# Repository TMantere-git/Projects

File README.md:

# Projects

Here is a compilation of projects I have been part of.

### 

Dartbot is a device that uses OpenGL to track a target and shoot a dart on it at a right distance. The target is taught to it using Haar Cascade. For moving it uses 4 DC motors, for target acquiring 2 servo motors, and for shooting the dart 2 dc motors and a solenoid. At a heart of the device lies a Raspberry Pi 3b and for camera it uses a regular Raspberry Pi camera.

Dartbot was part of a Amazing Robots competition hosted by Finnish TIETOTEKNIIKAN JA ELEKTRONIIKAN SEURA or SOCIETY OF INFORMATION TECHNOLOGY AND ELECTRONICS in which the robot came on the 4th position out of 10 competitors.

[Link to a News article about the competition](https://www.mikrobitti.fi/neuvot/robotit-kisasivat-messukeskuksessa-10-000-euron-voittopotti-tuli-ylivertaisella-teknisella-toteutuksella/60490a0f-0bc4-4c8e-a108-126306718576) (only in Finnish)

Picture of the Device

### 

Weatherstation is simple multidevice weather monitoring system. It uses multiple similar stations that are made of Adafruit Feather Huzzah ESP8266 boards with bme280 sensors to measure temperature, air pressure and air humidity. These measurements are then uploaded on a mySQL database every hour where they can be accessed by a website showing the data in raw form as well as in a graph.

Station-program runs on linux server that is self built, configurated and managed. On the server program does averaging of the measurements and a prediction of the weather using SARIMA model.

Website layout

### 

Basic snake type game using c#. To run the program run SnakeGame.exe from SnakeGame/bin/Release/publish/

Aim of the project was to learn some basic game-programming on C#

### 

TankkaajaPro is a self made android application to track car fueling statistics like kilometers driven, gas price, etc.
Application is done using dart and kotlin.
Application uses python api on a self made server to add and read data from mySQL database.

The aim of the project was to learn how to do android programming.

### 5 More to come...

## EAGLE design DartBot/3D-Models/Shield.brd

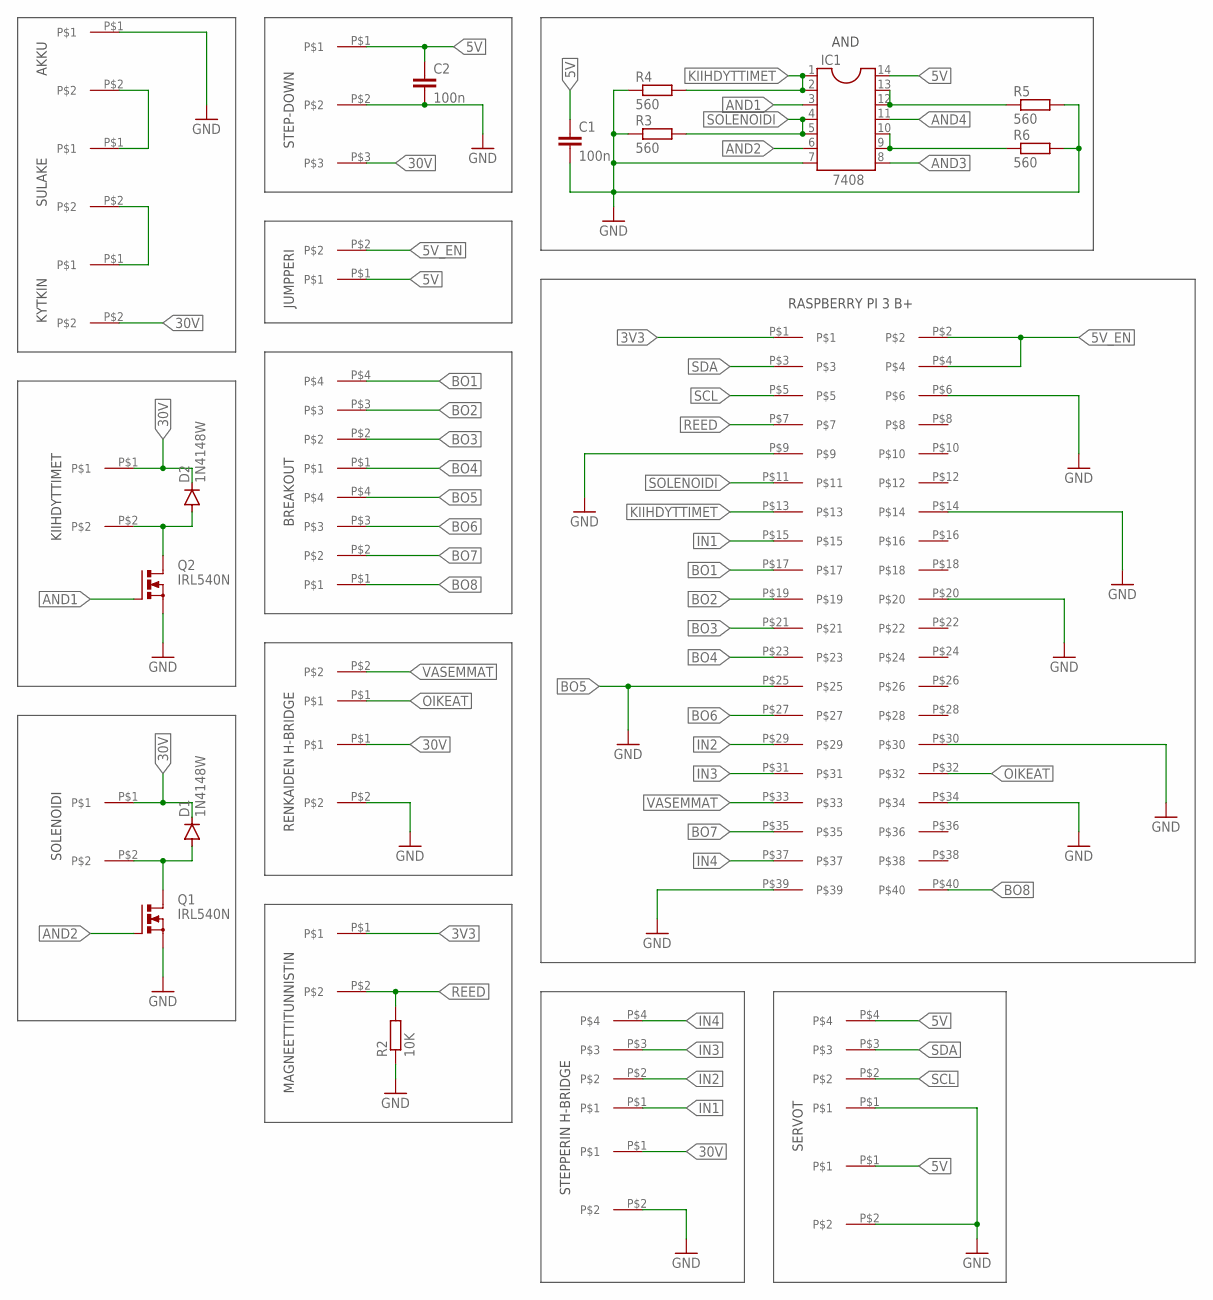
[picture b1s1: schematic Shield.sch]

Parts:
AKKU: AKKU; 2PIN
C1, C2: 100n; C1206
D1, D2: 1N4148W; SOD-123_MINI-SMA
IC1: 7408; DIL14
Q1, Q2: IRL540N; TO220BH
R2: 10K; M1206
R3, R4, R5, R6: 560; M1206
U$1: KIIHDYTTIMET; 2PIN
U$2: SOLENOIDI; 2PIN
U$3: 2.54_4PIN
U$4: SULAKE; 2PIN
U$5: KYTKIN; 2PIN
U$6: REED; 2PIN
U$7: STEP-DOWN; 3PIN
U$8: STEPPER; 2PIN
U$9: RENKAAT; 2PIN
U$10, U$11: 2.54_2PIN2PIN; 2.54_2PIN
U$12, U$15, U$16: SERVO; 2.54_4PIN
U$13: SERVO; 2PIN
U$14: PI3

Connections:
3V3: U$6.P$1, U$14.P$1
5V: C1.1, C2.1, IC1.14, U$7.P$1, U$11.P$1, U$12.P$4, U$13.P$1
5V_EN: U$11.P$2, U$14.P$2, U$14.P$4
30V: D1.C, D2.C, U$1.P$1, U$2.P$1, U$5.P$2, U$7.P$3, U$8.P$1, U$9.P$1
AND1: IC1.3, Q2.G
AND2: IC1.6, Q1.G
AND3: IC1.8
AND4: IC1.11
BO1: U$14.P$17, U$15.P$4
BO2: U$14.P$19, U$15.P$3
BO3: U$14.P$21, U$15.P$2
BO4: U$14.P$23, U$15.P$1
BO5: U$14.P$25, U$16.P$4
BO6: U$14.P$27, U$16.P$3
BO7: U$14.P$35, U$16.P$2
BO8: U$14.P$40, U$16.P$1
GND: AKKU.P$1, C1.2, C2.2, IC1.7, Q1.S, Q2.S, R2.1, R3.1, R4.1, R5.2, R6.2, U$7.P$2, U$8.P$2, U$9.P$2, U$12.P$1, U$13.P$2, U$14.P$6, U$14.P$9, U$14.P$14, U$14.P$20, U$14.P$30, U$14.P$34, U$14.P$39
IN1: U$3.P$1, U$14.P$15
IN2: U$3.P$2, U$14.P$29
IN3: U$3.P$3, U$14.P$31
IN4: U$3.P$4, U$14.P$37
KIIHDYTTIMET: IC1.1, IC1.2, R4.2, U$14.P$13
unnamed: D2.A, Q2.D, U$1.P$2
unnamed: IC1.9, IC1.10, R6.1
unnamed: IC1.12, IC1.13, R5.1
unnamed: D1.A, Q1.D, U$2.P$2
unnamed: AKKU.P$2, U$4.P$1
unnamed: U$4.P$2, U$5.P$1
OIKEAT: U$10.P$1, U$14.P$32
REED: R2.2, U$6.P$2, U$14.P$7
SCL: U$12.P$2, U$14.P$5
SDA: U$12.P$3, U$14.P$3
SOLENOIDI: IC1.4, IC1.5, R3.2, U$14.P$11
VASEMMAT: U$10.P$2, U$14.P$33

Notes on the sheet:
KIIHDYTTIMET
SOLENOIDI
AND
AKKU
SULAKE
KYTKIN
STEP-DOWN
STEPPERIN H-BRIDGE
RENKAIDEN H-BRIDGE
JUMPPERI
BREAKOUT
SERVOT
MAGNEETTITUNNISTIN
RASPBERRY PI 3 B+

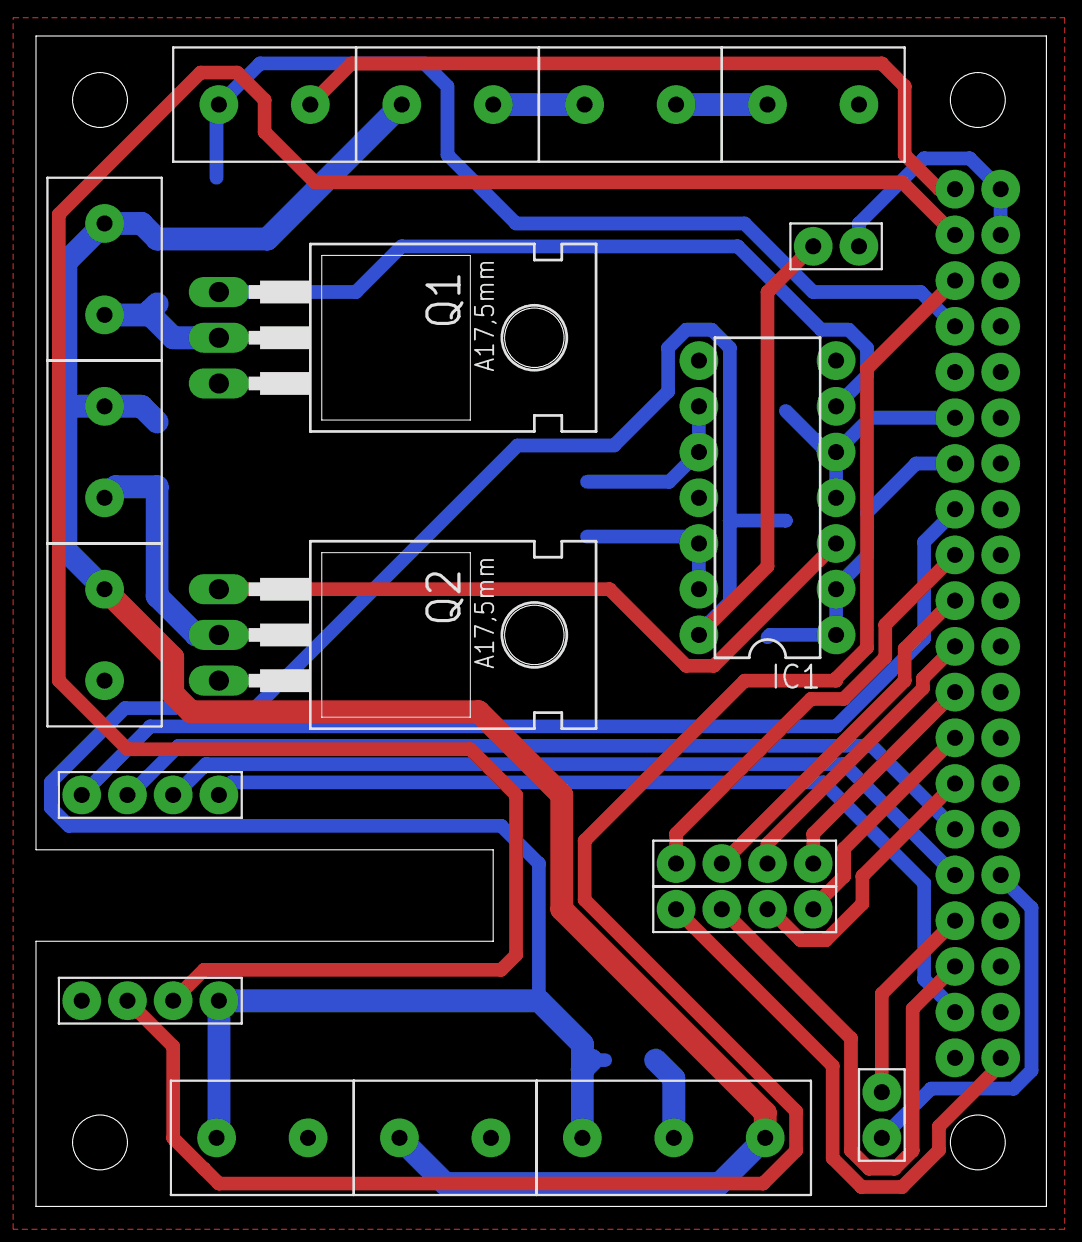
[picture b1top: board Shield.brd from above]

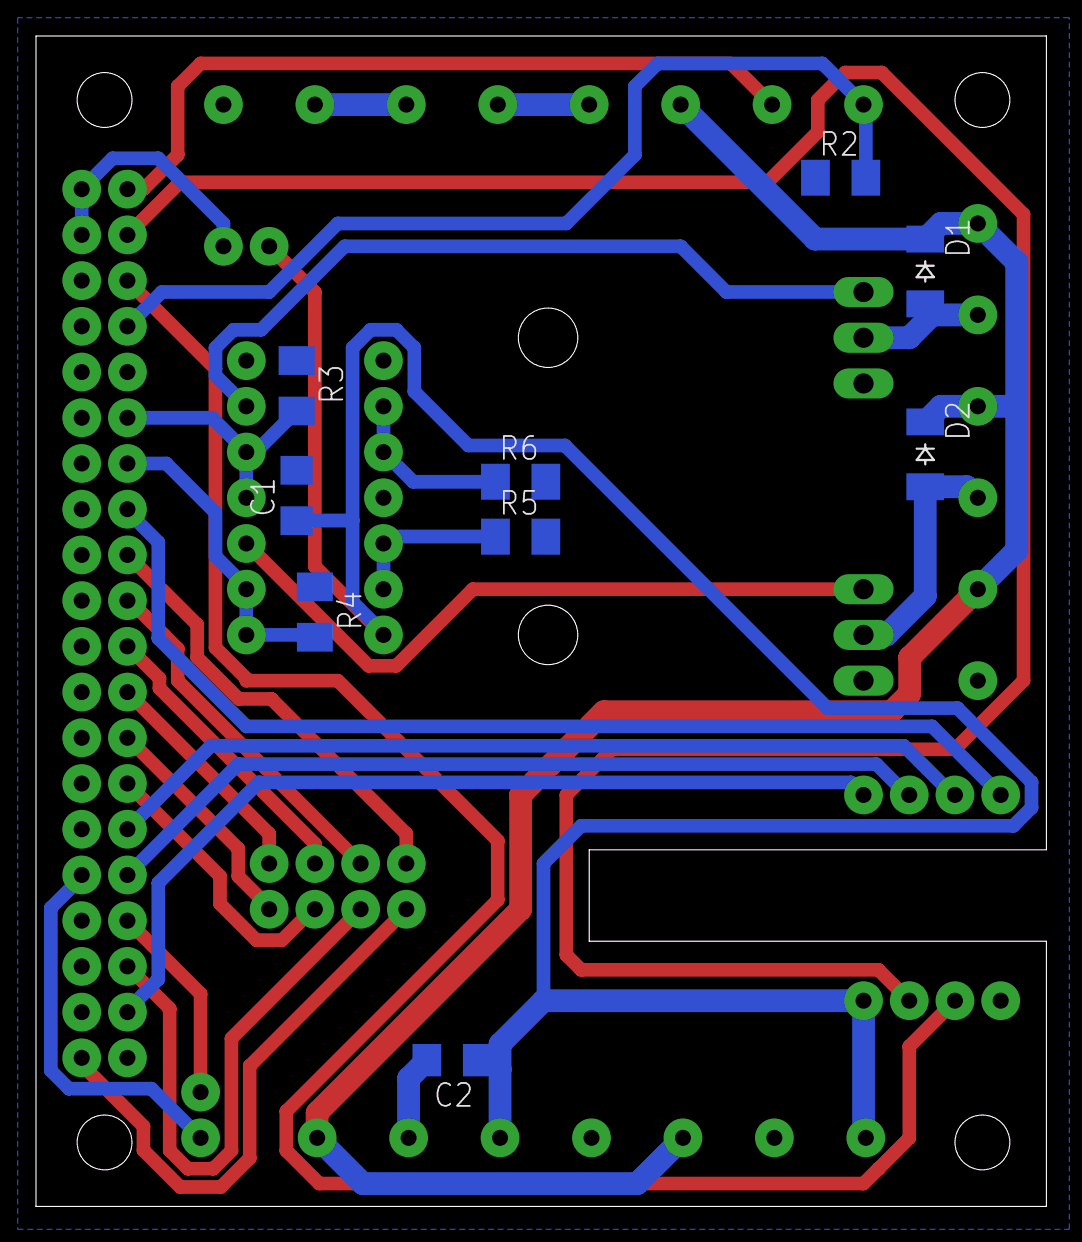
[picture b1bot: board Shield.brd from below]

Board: 2 copper layers, 56.1 x 65.0 mm, 29 parts (9 on the bottom side), 32 nets.

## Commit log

2020-01-26 Create Weatherstation
2020-01-26 Rename Weatherstation to WeatherStation/Weatherstation
2020-01-26 Create placeholder
2020-01-26 Create radme
2023-09-05 index commit
2023-09-13 Added snake game and .gitignore
2023-09-13 Adeded snake game
2023-09-13 Pages (#2)
    * Added snake game and .gitignore
    * Adeded snake game
2023-09-13 Update README.md (#3)
2023-09-13 added standalone .exe
2023-09-13 snakegame
2023-09-13 Update README.md (#4)
2023-09-13 Pages (#5)
    * Added snake game and .gitignore
    * Adeded snake game
    * added standalone .exe
    * commit
    * snakegame
    * fix
2023-09-14 added tankkaajapro
2023-09-14 add tankkaajapro
2023-09-14 remove sensitive information
